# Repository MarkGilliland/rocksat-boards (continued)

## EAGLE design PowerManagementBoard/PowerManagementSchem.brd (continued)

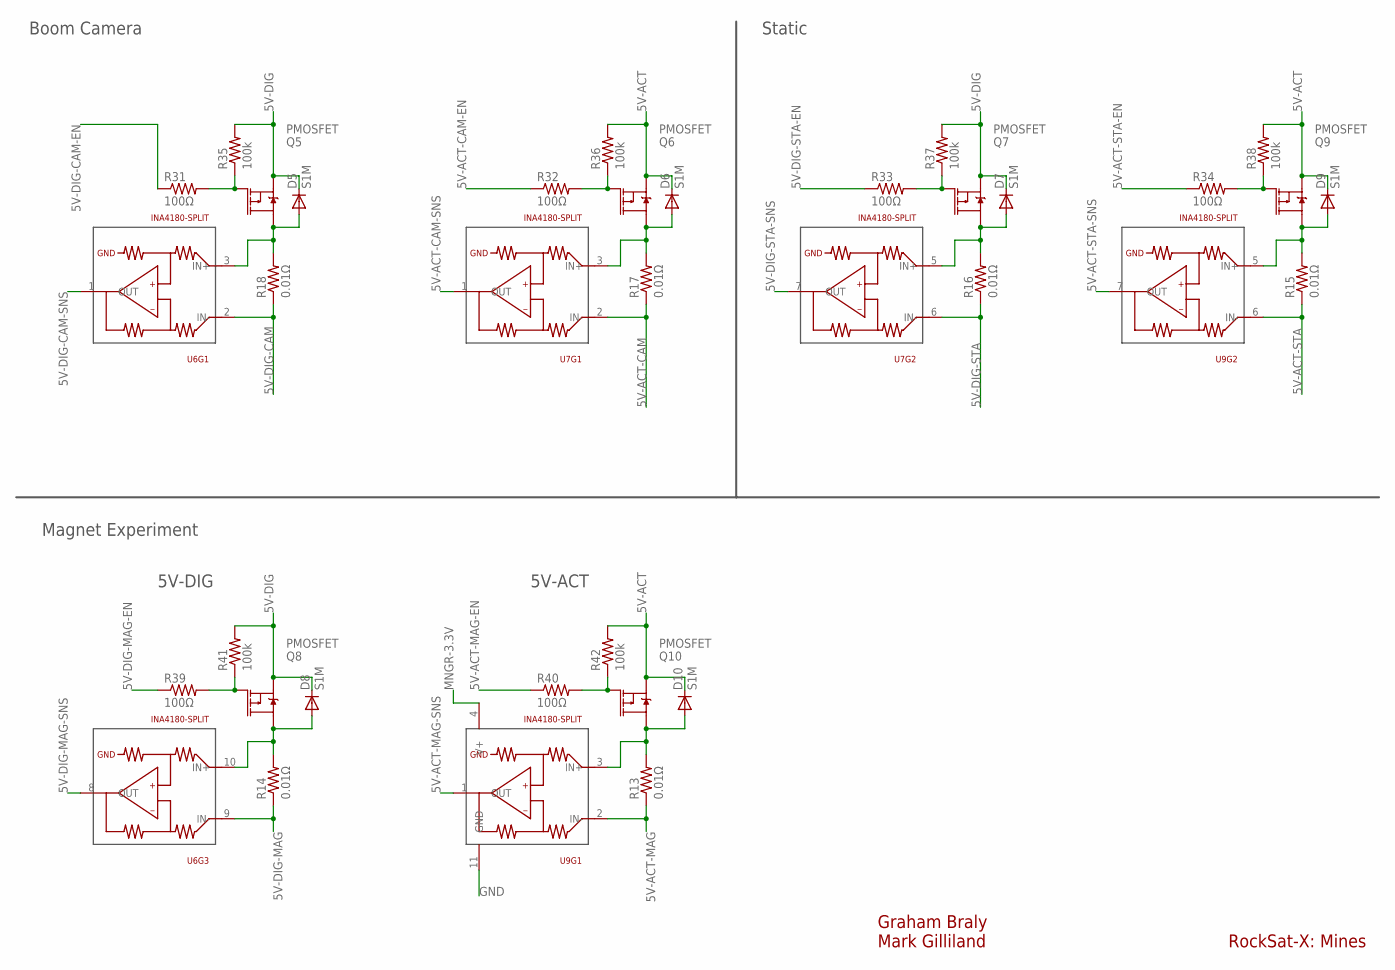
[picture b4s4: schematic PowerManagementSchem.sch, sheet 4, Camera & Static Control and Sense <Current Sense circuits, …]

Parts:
D5, D6, D7, D8, D9, D10: S1M; SMA
Q5, Q6, Q7, Q8, Q9, Q10: PMOSFET; DPAK
R13, R14, R15, R16, R17, R18: 0.01Ω; R1206
R31, R32, R33, R34, R39, R40: 100Ω; R0805
R35, R36, R37, R38, R41, R42: 100k; R0805
U6, U7, U9: INA4180-SPLIT; TSSOP14

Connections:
5V-ACT: D6.C, D9.C, D10.C, Q6.3 (S), Q9.3 (S), Q10.3 (S), R36.2, R38.2, R42.2; also elsewhere on the board
5V-ACT-CAM: R17.1, U7.2 (IN-); also elsewhere on the board
5V-ACT-CAM-EN: R32.1; also elsewhere on the board
5V-ACT-CAM-SNS: U7.1 (OUT); also elsewhere on the board
5V-ACT-MAG: R13.1, U9.2 (IN-); also elsewhere on the board
5V-ACT-MAG-EN: R40.1; also elsewhere on the board
5V-ACT-MAG-SNS: U9.1 (OUT); also elsewhere on the board
5V-ACT-STA: R15.1, U9.6 (IN-); also elsewhere on the board
5V-ACT-STA-EN: R34.1; also elsewhere on the board
5V-ACT-STA-SNS: U9.7 (OUT); also elsewhere on the board
5V-DIG: D5.C, D7.C, D8.C, Q5.3 (S), Q7.3 (S), Q8.3 (S), R35.2, R37.2, R41.2; also elsewhere on the board
5V-DIG-CAM: R18.1, U6.2 (IN-); also elsewhere on the board
5V-DIG-CAM-EN: R31.1; also elsewhere on the board
5V-DIG-CAM-SNS: U6.1 (OUT); also elsewhere on the board
5V-DIG-MAG: R14.1, U6.9 (IN-); also elsewhere on the board
5V-DIG-MAG-EN: R39.1; also elsewhere on the board
5V-DIG-MAG-SNS: U6.8 (OUT); also elsewhere on the board
5V-DIG-STA: R16.1, U7.6 (IN-); also elsewhere on the board
5V-DIG-STA-EN: R33.1; also elsewhere on the board
5V-DIG-STA-SNS: U7.7 (OUT); also elsewhere on the board
GND: U9.11 (GND); also elsewhere on the board
MNGR-3.3V: U9.4 (V+); also elsewhere on the board
unnamed: Q10.1 (G), R40.2, R42.1
unnamed: D10.A, Q10.4 (D), R13.2, U9.3 (IN+)
unnamed: Q8.1 (G), R39.2, R41.1
unnamed: D8.A, Q8.4 (D), R14.2, U6.10 (IN+)
unnamed: Q9.1 (G), R34.2, R38.1
unnamed: D9.A, Q9.4 (D), R15.2, U9.5 (IN+)
unnamed: Q7.1 (G), R33.2, R37.1
unnamed: D7.A, Q7.4 (D), R16.2, U7.5 (IN+)
unnamed: Q6.1 (G), R32.2, R36.1
unnamed: D6.A, Q6.4 (D), R17.2, U7.3 (IN+)
unnamed: Q5.1 (G), R31.2, R35.1
unnamed: D5.A, Q5.4 (D), R18.2, U6.3 (IN+)

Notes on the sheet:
5V-ACT
5V-DIG
Graham Braly Mark Gilliland
RockSat-X: Mines
Boom Camera
Static
Magnet Experiment

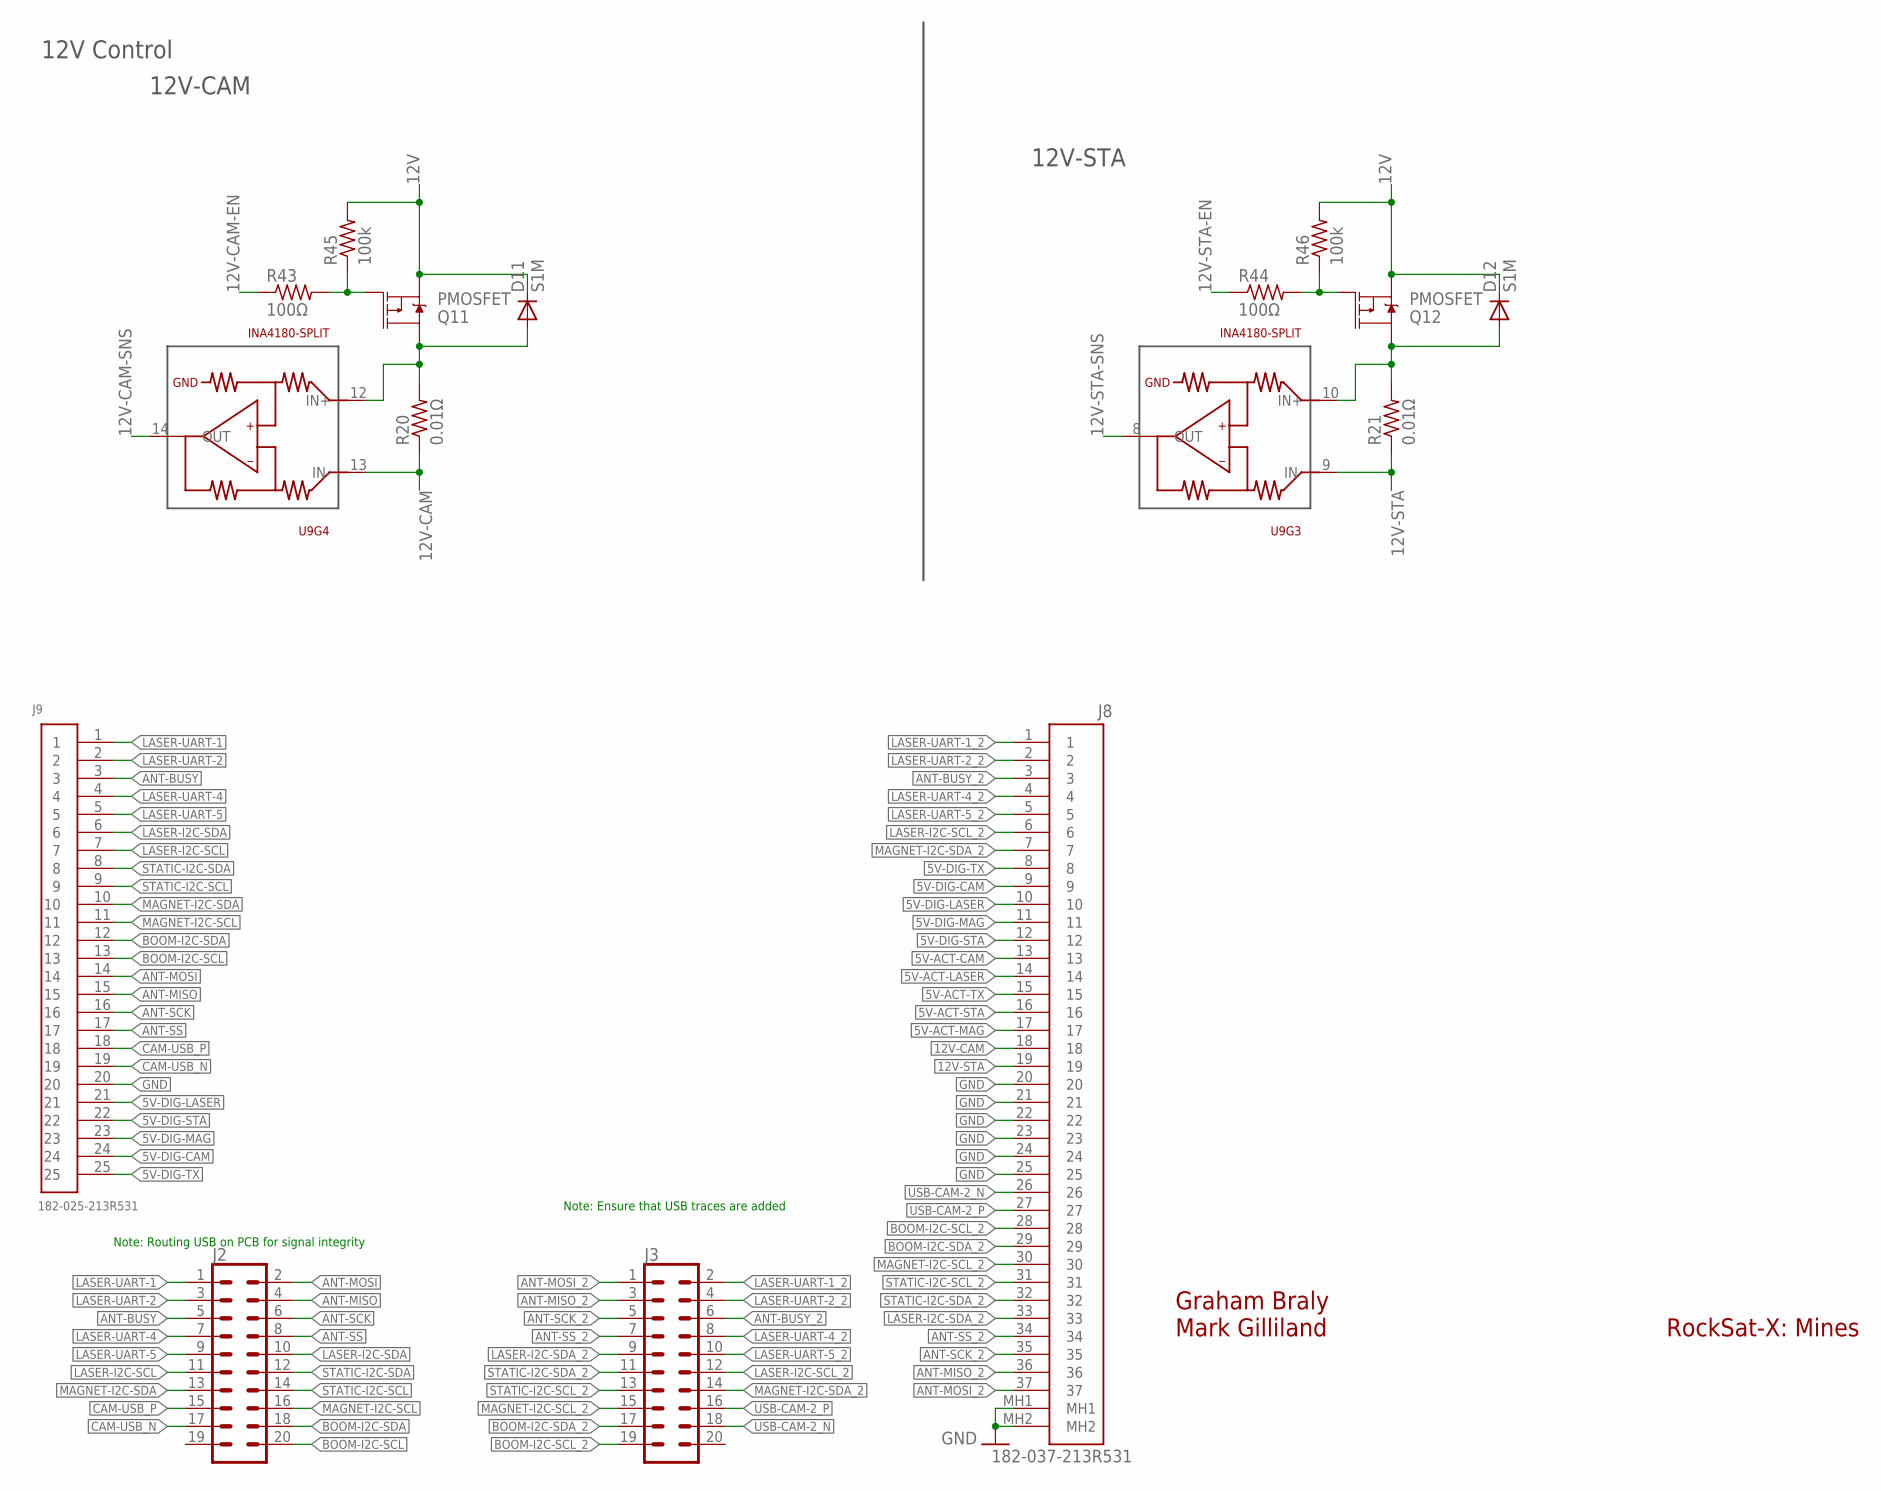
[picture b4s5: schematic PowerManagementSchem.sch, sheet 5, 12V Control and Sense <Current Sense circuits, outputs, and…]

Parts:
D11, D12: S1M; SMA
J2, J3: CONN_10X22X10_LOCK; 2X10_LOCK
J8: 182-037-213R531
J9: 182-025-213R531
Q11, Q12: PMOSFET; DPAK
R20, R21: 0.01Ω; R1206
R43, R44: 100Ω; R0805
R45, R46: 100k; R0805
U9: INA4180-SPLIT; TSSOP14

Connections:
5V-ACT-CAM: J8.13; also elsewhere on the board
5V-ACT-LASER: J8.14; also elsewhere on the board
5V-ACT-MAG: J8.17; also elsewhere on the board
5V-ACT-STA: J8.16; also elsewhere on the board
5V-ACT-TX: J8.15; also elsewhere on the board
5V-DIG-CAM: J8.9, J9.24; also elsewhere on the board
5V-DIG-LASER: J8.10, J9.21; also elsewhere on the board
5V-DIG-MAG: J8.11, J9.23; also elsewhere on the board
5V-DIG-STA: J8.12, J9.22; also elsewhere on the board
5V-DIG-TX: J8.8, J9.25; also elsewhere on the board
12V: D11.C, D12.C, Q11.3 (S), Q12.3 (S), R45.2, R46.2; also elsewhere on the board
12V-CAM: J8.18, R20.1, U9.13 (IN-)
12V-CAM-EN: R43.1; also elsewhere on the board
12V-CAM-SNS: U9.14 (OUT); also elsewhere on the board
12V-STA: J8.19, R21.1, U9.9 (IN-)
12V-STA-EN: R44.1; also elsewhere on the board
12V-STA-SNS: U9.8 (OUT); also elsewhere on the board
ANT-BUSY: J2.5, J9.3
ANT-BUSY_2: J3.6, J8.3
ANT-MISO: J2.4, J9.15
ANT-MISO_2: J3.3, J8.36
ANT-MOSI: J2.2, J9.14
ANT-MOSI_2: J3.1, J8.37
ANT-SCK: J2.6, J9.16
ANT-SCK_2: J3.5, J8.35
ANT-SS: J2.8, J9.17
ANT-SS_2: J3.7, J8.34
BOOM-I2C-SCL: J2.20, J9.13
BOOM-I2C-SCL_2: J3.19, J8.28
BOOM-I2C-SDA: J2.18, J9.12
BOOM-I2C-SDA_2: J3.17, J8.29
CAM-USB_N: J2.17, J9.19
CAM-USB_P: J2.15, J9.18
GND: J8.20, J8.21, J8.22, J8.23, J8.24, J8.25, J8.MH1, J8.MH2, J9.20; also elsewhere on the board
LASER-I2C-SCL: J2.11, J9.7
LASER-I2C-SCL_2: J3.12, J8.6
LASER-I2C-SDA: J2.10, J9.6
LASER-I2C-SDA_2: J3.9, J8.33
LASER-UART-1: J2.1, J9.1
LASER-UART-1_2: J3.2, J8.1
LASER-UART-2: J2.3, J9.2
LASER-UART-2_2: J3.4, J8.2
LASER-UART-4: J2.7, J9.4
LASER-UART-4_2: J3.8, J8.4
LASER-UART-5: J2.9, J9.5
LASER-UART-5_2: J3.10, J8.5
MAGNET-I2C-SCL: J2.16, J9.11
MAGNET-I2C-SCL_2: J3.15, J8.30
MAGNET-I2C-SDA: J2.13, J9.10
MAGNET-I2C-SDA_2: J3.14, J8.7
unnamed: D11.A, Q11.4 (D), R20.2, U9.12 (IN+)
unnamed: D12.A, Q12.4 (D), R21.2, U9.10 (IN+)
unnamed: Q11.1 (G), R43.2, R45.1
unnamed: Q12.1 (G), R44.2, R46.1
STATIC-I2C-SCL: J2.14, J9.9
STATIC-I2C-SCL_2: J3.13, J8.31
STATIC-I2C-SDA: J2.12, J9.8
STATIC-I2C-SDA_2: J3.11, J8.32
USB-CAM-2_N: J3.18, J8.26
USB-CAM-2_P: J3.16, J8.27

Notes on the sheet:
Graham Braly Mark Gilliland
RockSat-X: Mines
12V-STA
12V-CAM
12V Control
Note: Routing USB on PCB for signal integrity
Note: Ensure that USB traces are added

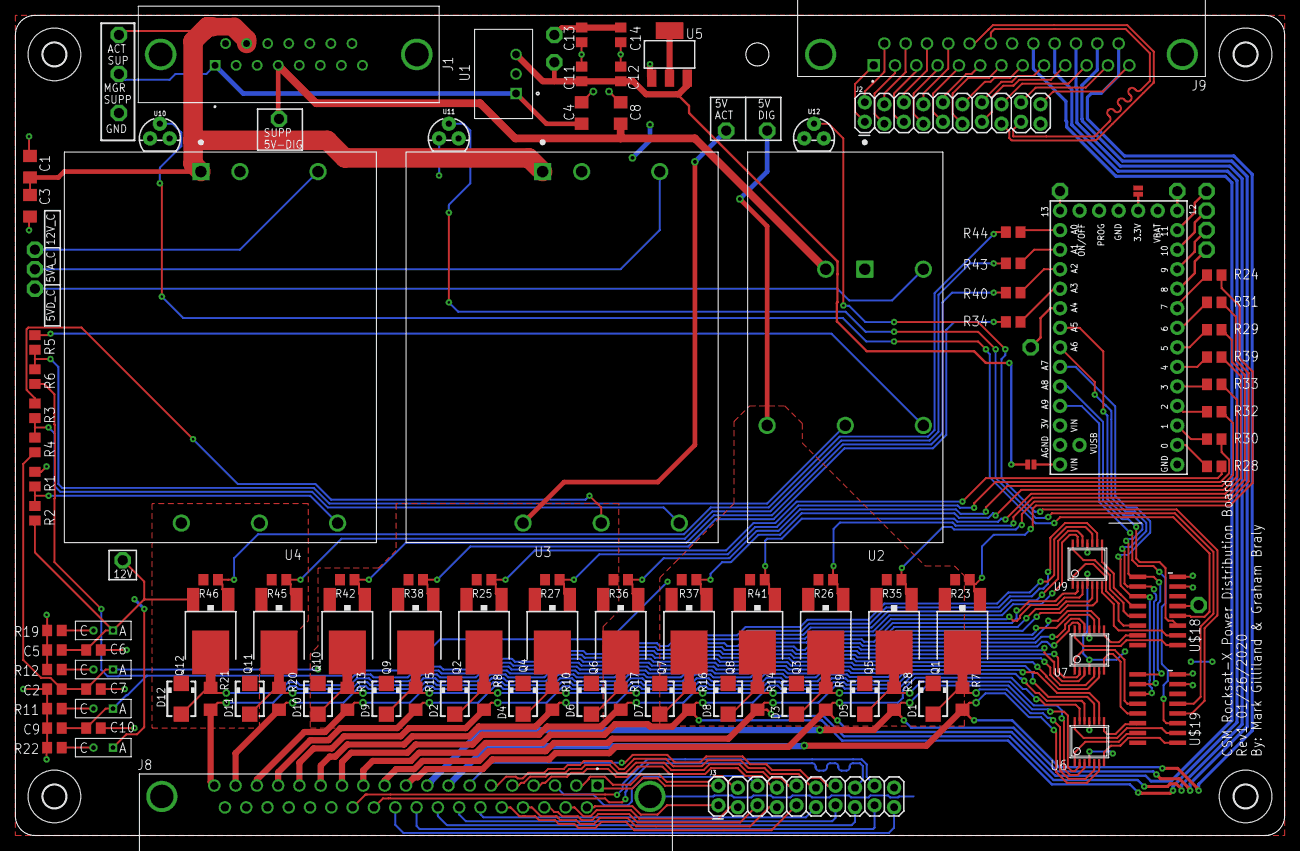
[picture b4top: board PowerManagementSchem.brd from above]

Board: 2 copper layers, 165.1 x 106.7 mm, 134 parts (1 on the bottom side), 137 nets.

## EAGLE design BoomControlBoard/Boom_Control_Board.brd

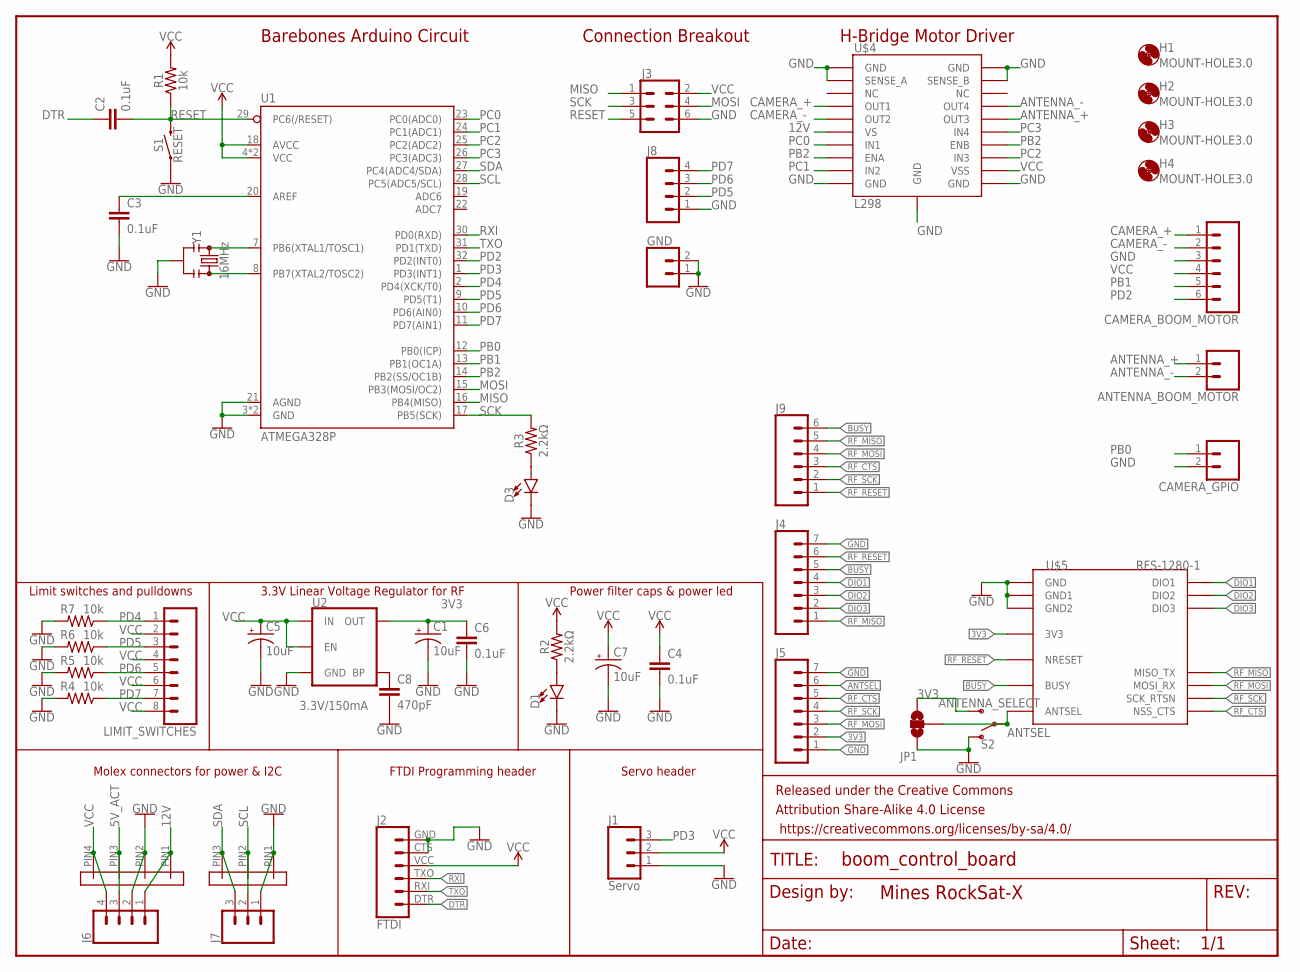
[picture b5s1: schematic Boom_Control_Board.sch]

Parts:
ANTENNA_BOOM_MOTOR: CONN_02LOCK_LONGPADS; 1X02_LOCK_LONGPADS
C1, C5, C7: 10uF; EIA3216
C2, C3, C4, C6: 0.1uF; 0805
C8: 470pF; 0805
CAMERA_BOOM_MOTOR: CONN_06LOCK_LONGPADS; 1X06_LOCK_LONGPADS
CAMERA_GPIO: CONN_02LOCK_LONGPADS; 1X02_LOCK_LONGPADS
D1, D3: LED-GREEN1206; LED-1206
FRAME1: FRAME-LETTERNO_PACKAGE; DUMMY
GND: CONN_02LOCK_LONGPADS; 1X02_LOCK_LONGPADS
H1, H2, H3, H4: MOUNT-HOLE3.0; 3,0
J1: Servo; 1X03
J2: FTDI; FTDI_BASIC
J3: CONN_03X22X3_SILK_MALE_PTH; 2X3
J4, J5: CONN_07LOCK; 1X07_LOCK
J6, J8: CONN_04LOCK; 1X04_LOCK
J7: CONN_03; 1X03
J9: CONN_06LOCK; 1X06_LOCK
JP1: JUMPER-SMT_3_NO_NO_SILK; SMT-JUMPER_3_0-NO_TRACE_NO-SILK
LIMIT_SWITCHES: CONN_08LOCK_LONGPADS; 1X08_LOCK_LONGPADS
R1, R4, R5, R6, R7: 10k; 0805
R2, R3: 2.2kΩ; 0805
S1: RESET; TACTILE_SWITCH_SMD_5.2MM
S2: ANTENNA_SELECT; SWITCH_SPDT_PTH_11.6X4.0MM
U1: ATMEGA328P; TQFP32-08
U2: 3.3V/150mA; SOT23-5
U$1: MOLEX_4PIN
U$2: MOLEX_3PIN
U$4: L298; POWERSO20_L298_PAD
U$5: RFS-1280-1
Y1: 16MHz; RESONATOR-SMD-3.2X1.3

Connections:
3V3: C1.+, C6.1, J5.2, JP1.3, S2.3 (S), U2.5 (OUT), U$5.P$9 (3V3), U$5.P$23 (3V3)
5V_ACT: J6.3, U$1.PIN3
12V: J6.1, U$1.PIN1, U$4.6 (VS)
ANTENNA_+: ANTENNA_BOOM_MOTOR.1, U$4.16 (OUT3)
ANTENNA_-: ANTENNA_BOOM_MOTOR.2, U$4.17 (OUT4)
ANTSEL: J5.6, JP1.2, S2.2, U$5.P$13 (ANTSEL), U$5.P$27 (ANTSEL)
BUSY: J4.5, J9.6, U$5.P$3 (BUSY), U$5.P$17 (BUSY)
CAMERA_+: CAMERA_BOOM_MOTOR.1, U$4.4 (OUT1)
CAMERA_-: CAMERA_BOOM_MOTOR.2, U$4.5 (OUT2)
DIO1: J4.4, U$5.P$4 (DIO1), U$5.P$18 (DIO1)
DIO2: J4.3, U$5.P$5 (DIO2), U$5.P$19 (DIO2)
DIO3: J4.2, U$5.P$6 (DIO3), U$5.P$20 (DIO3)
DTR: C2.1, J2.DTR (1)
GND: C1.-, C3.2, C4.2, C5.-, C6.2, C7.-, C8.2, CAMERA_BOOM_MOTOR.3, CAMERA_GPIO.2, D1.C, D3.C, GND.1, GND.2, J1.1, J2.CTS (5), J2.GND (6), J3.6, J4.7, J5.1, J5.7, J6.2, J7.1, J8.1, JP1.1, R4.2, R5.2, R6.2, R7.2, S1.1, S1.2 (1), S2.1 (O), U1.3 (GND), U1.5 (GND), U1.21 (AGND), U2.2 (GND), U$1.PIN2, U$2.PIN1, U$4.1 (GND), U$4.2 (SENSE_A), U$4.10 (GND), U$4.11 (GND), U$4.19 (SENSE_B), U$4.20 (GND), U$4.PAD (GND), U$5.P$1 (GND), U$5.P$8 (GND1), U$5.P$14 (GND2), U$5.P$15 (GND), U$5.P$22 (GND1), U$5.P$28 (GND2), Y1.2
MISO: J3.1, U1.16 (PB4(MISO))
MOSI: J3.4, U1.15 (PB3(MOSI/OC2))
unnamed: U1.7 (PB6(XTAL1/TOSC1)), Y1.1
unnamed: U1.8 (PB7(XTAL2/TOSC2)), Y1.3
unnamed: C3.1, U1.20 (AREF)
unnamed: D1.A, R2.1
unnamed: D3.A, R3.1
unnamed: C8.1, U2.4 (BP)
PB0: CAMERA_GPIO.1, U1.12 (PB0(ICP))
PB1: CAMERA_BOOM_MOTOR.5, U1.13 (PB1(OC1A))
PB2: U1.14 (PB2(SS/OC1B)), U$4.8 (ENA), U$4.14 (ENB)
PC0: U1.23 (PC0(ADC0)), U$4.7 (IN1)
PC1: U1.24 (PC1(ADC1)), U$4.9 (IN2)
PC2: U1.25 (PC2(ADC2)), U$4.13 (IN3)
PC3: U1.26 (PC3(ADC3)), U$4.15 (IN4)
PD2: CAMERA_BOOM_MOTOR.6, U1.32 (PD2(INT0))
PD3: J1.3, U1.1 (PD3(INT1))
PD4: LIMIT_SWITCHES.1, R7.1, U1.2 (PD4(XCK/T0))
PD5: J8.2, LIMIT_SWITCHES.3, R6.1, U1.9 (PD5(T1))
PD6: J8.3, LIMIT_SWITCHES.5, R5.1, U1.10 (PD6(AIN0))
PD7: J8.4, LIMIT_SWITCHES.7, R4.1, U1.11 (PD7(AIN1))
RESET: C2.2, J3.5, R1.1, S1.3 (2), S1.4 (2), U1.29 (PC6(/RESET))
RF_CTS: J5.5, J9.3, U$5.P$12 (NSS_CTS), U$5.P$26 (NSS_CTS)
RF_MISO: J4.1, J9.5, U$5.P$7 (MISO_TX), U$5.P$21 (MISO_TX)
RF_MOSI: J5.3, J9.4, U$5.P$10 (MOSI_RX), U$5.P$24 (MOSI_RX)
RF_RESET: J4.6, J9.1, U$5.P$2 (NRESET), U$5.P$16 (NRESET)
RF_SCK: J5.4, J9.2, U$5.P$11 (SCK_RTSN), U$5.P$25 (SCK_RTSN)
RXI: J2.TXO (3), U1.30 (PD0(RXD))
SCK: J3.3, R3.2, U1.17 (PB5(SCK))
SCL: J7.2, U1.28 (PC5(ADC5/SCL)), U$2.PIN2
SDA: J7.3, U1.27 (PC4(ADC4/SDA)), U$2.PIN3
TXO: J2.RXI (2), U1.31 (PD1(TXD))
VCC: C4.1, C5.+, C7.+, CAMERA_BOOM_MOTOR.4, J1.2, J2.VCC (4), J3.2, J6.4, LIMIT_SWITCHES.2, LIMIT_SWITCHES.4, LIMIT_SWITCHES.6, LIMIT_SWITCHES.8, R1.2, R2.2, U1.4 (VCC), U1.6 (VCC), U1.18 (AVCC), U2.1 (IN), U2.3 (EN), U$1.PIN4, U$4.12 (VSS)

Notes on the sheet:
Molex connectors for power & I2C
FTDI Programming header
Servo header
Power filter caps & power led
Barebones Arduino Circuit
H-Bridge Motor Driver
Connection Breakout
Limit switches and pulldowns
3.3V Linear Voltage Regulator for RF

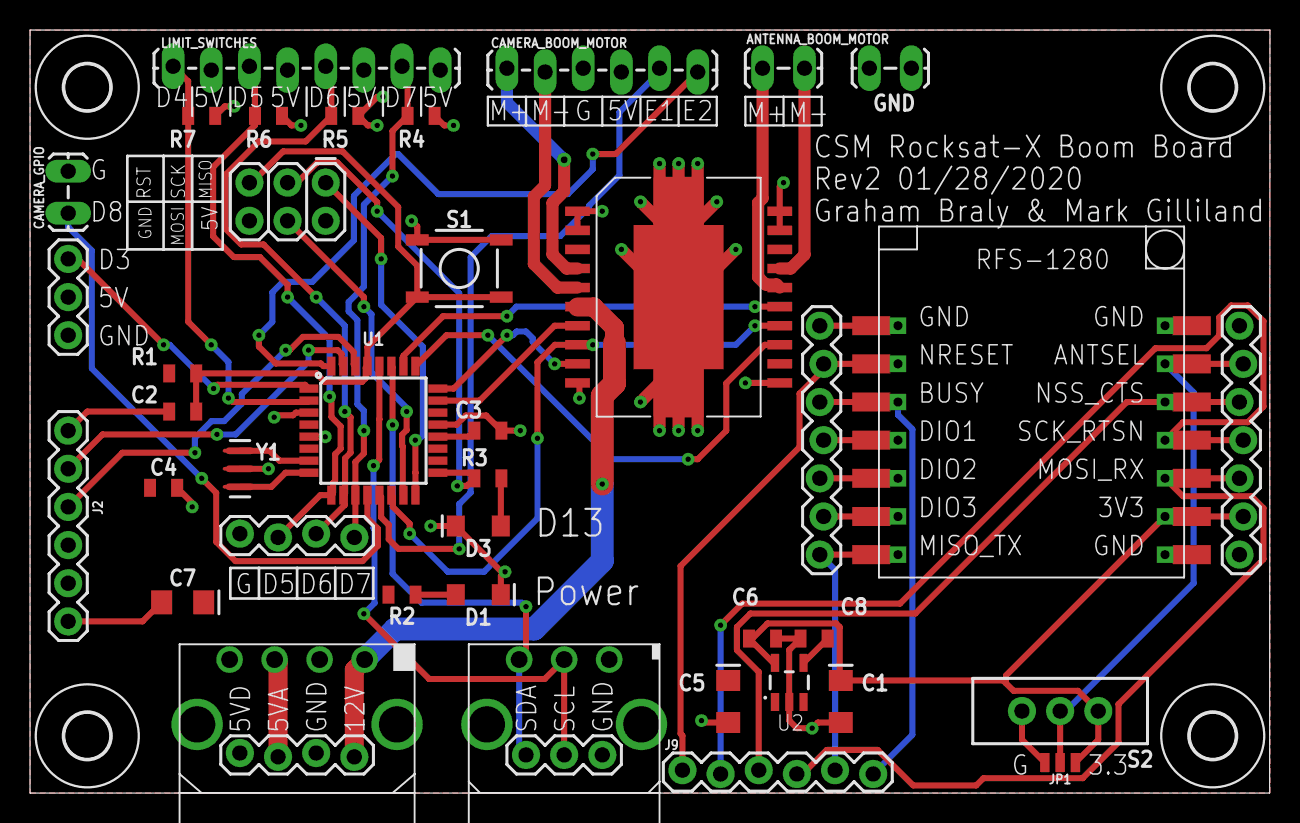
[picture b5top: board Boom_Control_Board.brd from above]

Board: 2 copper layers, 82.5 x 50.8 mm, 46 parts (0 on the bottom side), 47 nets.

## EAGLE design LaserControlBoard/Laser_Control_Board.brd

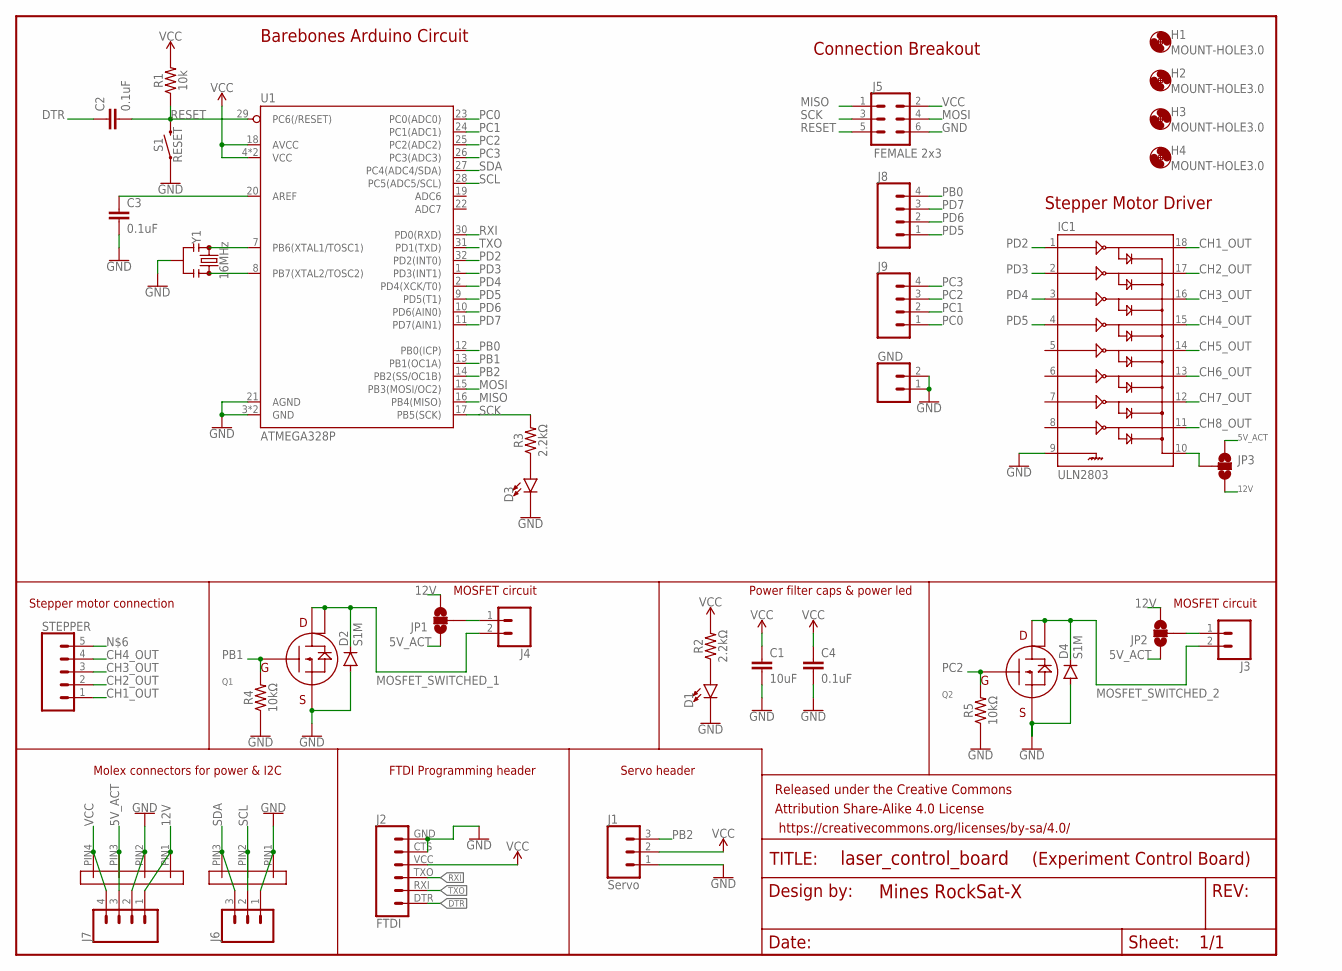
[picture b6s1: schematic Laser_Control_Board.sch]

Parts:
C1: 10uF; 0805
C2, C3, C4: 0.1uF; 0805
D1, D3: LED-GREEN1206; LED-1206
D2, D4: S1M; SMA
FRAME1: FRAME-LETTERNO_PACKAGE; DUMMY
GND: CONN_02LOCK_LONGPADS; 1X02_LOCK_LONGPADS
H1, H2, H3, H4: MOUNT-HOLE3.0; 3,0
IC1: ULN2803; SO18L
J1: Servo; 1X03
J2: FTDI; FTDI_BASIC
J3, J4: CONN_02; 1X02
J5: FEMALE 2x3; 2X3
J6: CONN_03; 1X03
J7, J8, J9: CONN_04LOCK; 1X04_LOCK
JP1, JP2, JP3: JUMPER-SMT_3_NO_NO_SILK; SMT-JUMPER_3_0-NO_TRACE_NO-SILK
Q1, Q2: BUK9880-55A; SOT223
R1: 10k; 0805
R2, R3: 2.2kΩ; 0805
R4, R5: 10kΩ; 0805
S1: RESET; TACTILE_SWITCH_SMD_5.2MM
STEPPER: CONN_05; 1X05
U1: ATMEGA328P; TQFP32-08
U$1: MOLEX_4PIN
U$2: MOLEX_3PIN
Y1: 16MHz; RESONATOR-SMD-3.2X1.3

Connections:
5V_ACT: J7.3, JP1.1, JP2.1, JP3.1, U$1.PIN3
12V: J7.1, JP1.3, JP2.3, JP3.3, U$1.PIN1
CH1_OUT: IC1.18, STEPPER.1
CH2_OUT: IC1.17, STEPPER.2
CH3_OUT: IC1.16, STEPPER.3
CH4_OUT: IC1.15, STEPPER.4
CH5_OUT: IC1.14
CH6_OUT: IC1.13
CH7_OUT: IC1.12
CH8_OUT: IC1.11
DTR: C2.1, J2.DTR (1)
GND: C1.2, C3.2, C4.2, D1.C, D2.A, D3.C, D4.A, GND.1, GND.2, IC1.9, J1.1, J2.CTS (5), J2.GND (6), J5.6, J6.1, J7.2, Q1.3 (SOURCE), Q2.3 (SOURCE), R4.1, R5.1, S1.1, S1.2 (1), U1.3 (GND), U1.5 (GND), U1.21 (AGND), U$1.PIN2, U$2.PIN1, Y1.2
MISO: J5.1, U1.16 (PB4(MISO))
MOSFET_SWITCHED_1: D2.C, J4.2, Q1.2 (DRAIN), Q1.4 (DRAIN_TAB)
MOSFET_SWITCHED_2: D4.C, J3.2, Q2.2 (DRAIN), Q2.4 (DRAIN_TAB)
MOSI: J5.4, U1.15 (PB3(MOSI/OC2))
unnamed: J4.1, JP1.2
unnamed: U1.7 (PB6(XTAL1/TOSC1)), Y1.1
unnamed: U1.8 (PB7(XTAL2/TOSC2)), Y1.3
unnamed: C3.1, U1.20 (AREF)
unnamed: D1.A, R2.1
unnamed: IC1.10, JP3.2, STEPPER.5
unnamed: D3.A, R3.1
unnamed: J3.1, JP2.2
PB0: J8.4, U1.12 (PB0(ICP))
PB1: Q1.1 (GATE), R4.2, U1.13 (PB1(OC1A))
PB2: J1.3, U1.14 (PB2(SS/OC1B))
PC0: J9.1, U1.23 (PC0(ADC0))
PC1: J9.2, U1.24 (PC1(ADC1))
PC2: J9.3, Q2.1 (GATE), R5.2, U1.25 (PC2(ADC2))
PC3: J9.4, U1.26 (PC3(ADC3))
PD2: IC1.1, U1.32 (PD2(INT0))
PD3: IC1.2, U1.1 (PD3(INT1))
PD4: IC1.3, U1.2 (PD4(XCK/T0))
PD5: IC1.4, J8.1, U1.9 (PD5(T1))
PD6: J8.2, U1.10 (PD6(AIN0))
PD7: J8.3, U1.11 (PD7(AIN1))
RESET: C2.2, J5.5, R1.1, S1.3 (2), S1.4 (2), U1.29 (PC6(/RESET))
RXI: J2.TXO (3), U1.30 (PD0(RXD))
SCK: J5.3, R3.2, U1.17 (PB5(SCK))
SCL: J6.2, U1.28 (PC5(ADC5/SCL)), U$2.PIN2
SDA: J6.3, U1.27 (PC4(ADC4/SDA)), U$2.PIN3
TXO: J2.RXI (2), U1.31 (PD1(TXD))
VCC: C1.1, C4.1, J1.2, J2.VCC (4), J5.2, J7.4, R1.2, R2.2, U1.4 (VCC), U1.6 (VCC), U1.18 (AVCC), U$1.PIN4

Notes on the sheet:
Molex connectors for power & I2C
FTDI Programming header
Servo header
Stepper motor connection
MOSFET circuit
Power filter caps & power led
Barebones Arduino Circuit
Stepper Motor Driver
Connection Breakout
(Experiment Control Board)

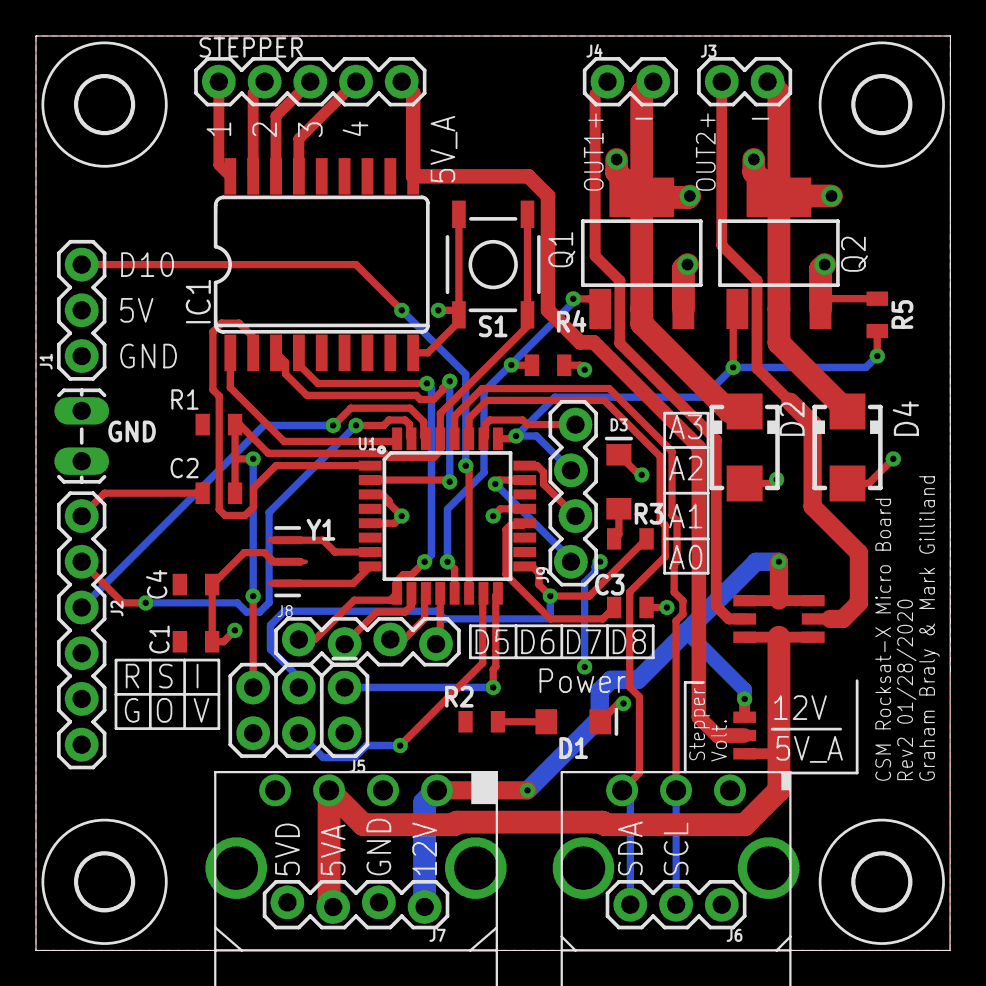
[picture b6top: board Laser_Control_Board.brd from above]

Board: 2 copper layers, 50.8 x 50.8 mm, 40 parts (0 on the bottom side), 40 nets.

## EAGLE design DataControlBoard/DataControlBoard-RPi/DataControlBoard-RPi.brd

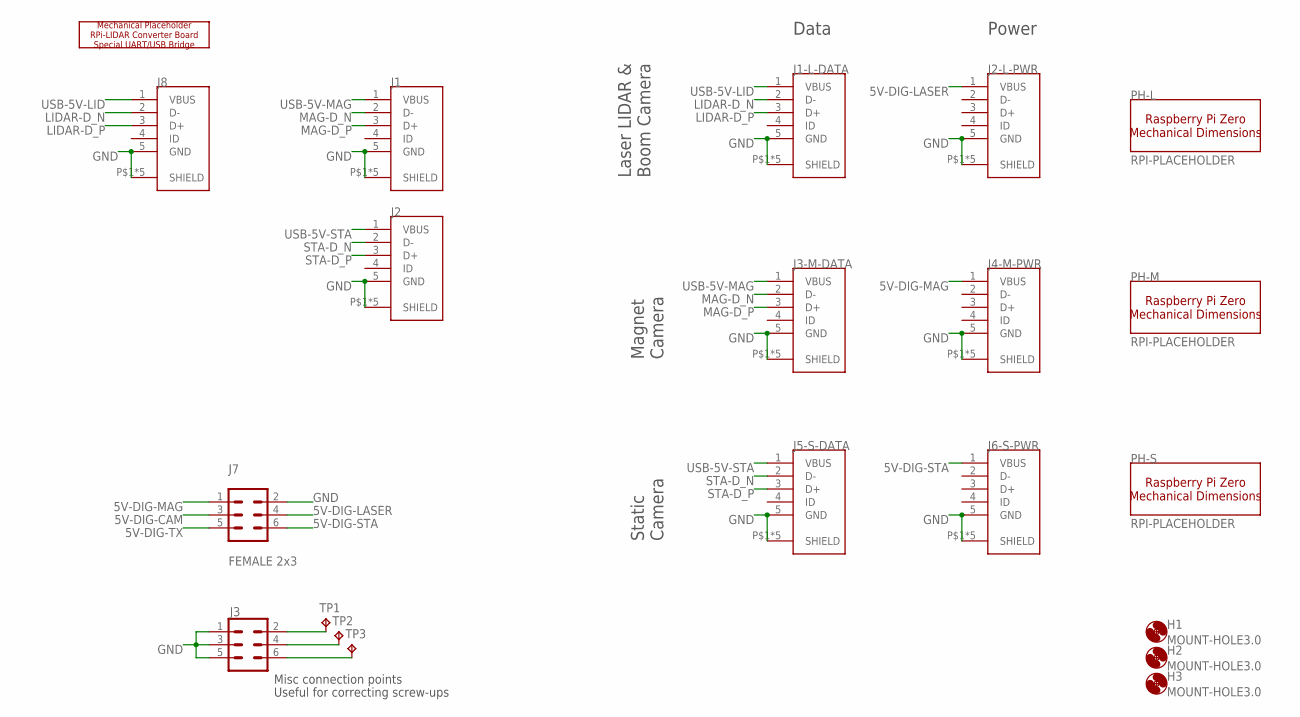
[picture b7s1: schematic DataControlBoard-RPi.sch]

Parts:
H1, H2, H3: MOUNT-HOLE3.0; 3,0
J1, J1-L-DATA, J2, J2-L-PWR, J3-M-DATA, J4-M-PWR, J5-S-DATA, J6-S-PWR, J8: USB3150-30-130-AMANUFACTURABLE; GCT_USB3150-30-EASIER
J3: CONN_03X22X3_SILK_MALE_PTH; 2X3
J7: FEMALE 2x3; 2X3
PH-L: RPI-PLACEHOLDER; RPI-ZERO-EDGE
PH-M: RPI-PLACEHOLDER; RPI-ZERO-EDGE
PH-S: RPI-PLACEHOLDER; RPI-ZERO-EDGE
TP1, TP2, TP3: TPPAD1-17; P1-17
U$4: LIDAR-CONV-PLACEHOLDER; LIDAR-PLACEHOLDER

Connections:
5V-DIG-CAM: J7.3
5V-DIG-LASER: J2-L-PWR.1 (VBUS), J7.4
5V-DIG-MAG: J4-M-PWR.1 (VBUS), J7.1
5V-DIG-STA: J6-S-PWR.1 (VBUS), J7.6
5V-DIG-TX: J7.5
GND: J1.5 (GND), J1.P$1 (SHIELD), J1.S3 (SHIELD), J1.S4 (SHIELD), J1.S5 (SHIELD), J1.S6 (SHIELD), J1-L-DATA.5 (GND), J1-L-DATA.P$1 (SHIELD), J1-L-DATA.S3 (SHIELD), J1-L-DATA.S4 (SHIELD), J1-L-DATA.S5 (SHIELD), J1-L-DATA.S6 (SHIELD), J2.5 (GND), J2.P$1 (SHIELD), J2.S3 (SHIELD), J2.S4 (SHIELD), J2.S5 (SHIELD), J2.S6 (SHIELD), J2-L-PWR.5 (GND), J2-L-PWR.P$1 (SHIELD), J2-L-PWR.S3 (SHIELD), J2-L-PWR.S4 (SHIELD), J2-L-PWR.S5 (SHIELD), J2-L-PWR.S6 (SHIELD), J3.1, J3.3, J3.5, J3-M-DATA.5 (GND), J3-M-DATA.P$1 (SHIELD), J3-M-DATA.S3 (SHIELD), J3-M-DATA.S4 (SHIELD), J3-M-DATA.S5 (SHIELD), J3-M-DATA.S6 (SHIELD), J4-M-PWR.5 (GND), J4-M-PWR.P$1 (SHIELD), J4-M-PWR.S3 (SHIELD), J4-M-PWR.S4 (SHIELD), J4-M-PWR.S5 (SHIELD), J4-M-PWR.S6 (SHIELD), J5-S-DATA.5 (GND), J5-S-DATA.P$1 (SHIELD), J5-S-DATA.S3 (SHIELD), J5-S-DATA.S4 (SHIELD), J5-S-DATA.S5 (SHIELD), J5-S-DATA.S6 (SHIELD), J6-S-PWR.5 (GND), J6-S-PWR.P$1 (SHIELD), J6-S-PWR.S3 (SHIELD), J6-S-PWR.S4 (SHIELD), J6-S-PWR.S5 (SHIELD), J6-S-PWR.S6 (SHIELD), J7.2, J8.5 (GND), J8.P$1 (SHIELD), J8.S3 (SHIELD), J8.S4 (SHIELD), J8.S5 (SHIELD), J8.S6 (SHIELD)
LIDAR-D_N: J1-L-DATA.2 (D-), J8.2 (D-)
LIDAR-D_P: J1-L-DATA.3 (D+), J8.3 (D+)
MAG-D_N: J1.2 (D-), J3-M-DATA.2 (D-)
MAG-D_P: J1.3 (D+), J3-M-DATA.3 (D+)
unnamed: J3.2, TP1.TP
unnamed: J3.4, TP2.TP
unnamed: J3.6, TP3.TP
STA-D_N: J2.2 (D-), J5-S-DATA.2 (D-)
STA-D_P: J2.3 (D+), J5-S-DATA.3 (D+)
USB-5V-LID: J1-L-DATA.1 (VBUS), J8.1 (VBUS)
USB-5V-MAG: J1.1 (VBUS), J3-M-DATA.1 (VBUS)
USB-5V-STA: J2.1 (VBUS), J5-S-DATA.1 (VBUS)

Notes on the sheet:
Laser LIDAR & Boom Camera
Magnet Camera
Static Camera
Power
Data
Misc connection points
Useful for correcting screw-ups

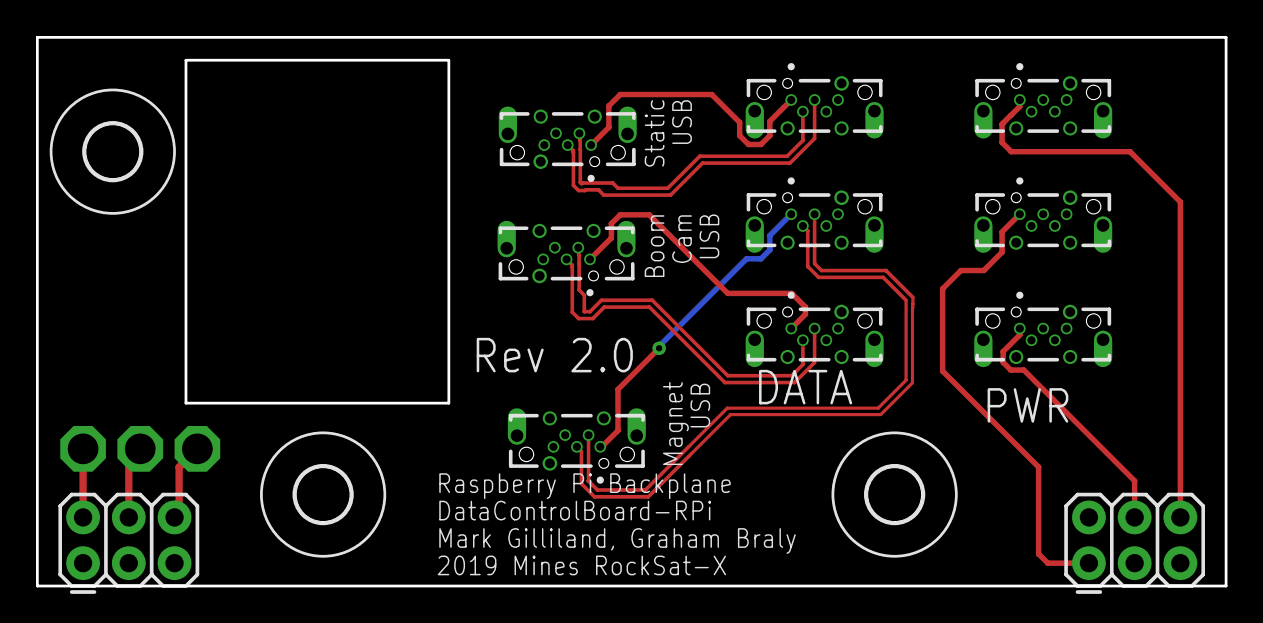
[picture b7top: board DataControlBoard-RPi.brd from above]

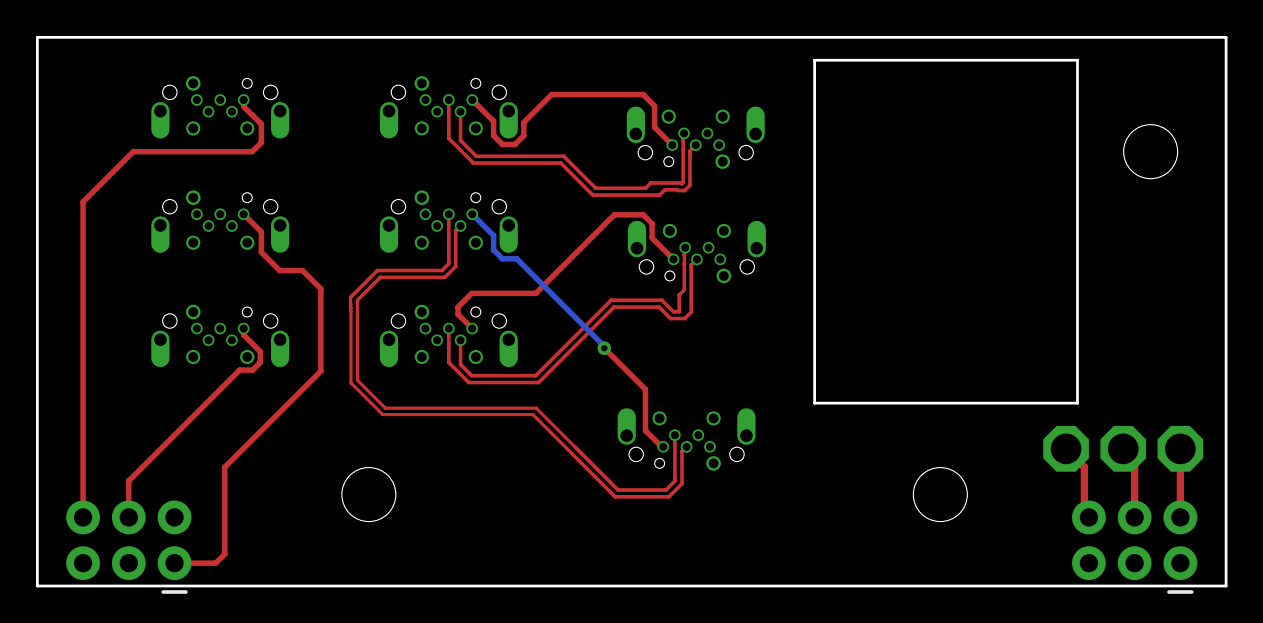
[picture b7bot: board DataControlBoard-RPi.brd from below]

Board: 2 copper layers, 66.0 x 30.5 mm, 21 parts (3 on the bottom side), 16 nets.
